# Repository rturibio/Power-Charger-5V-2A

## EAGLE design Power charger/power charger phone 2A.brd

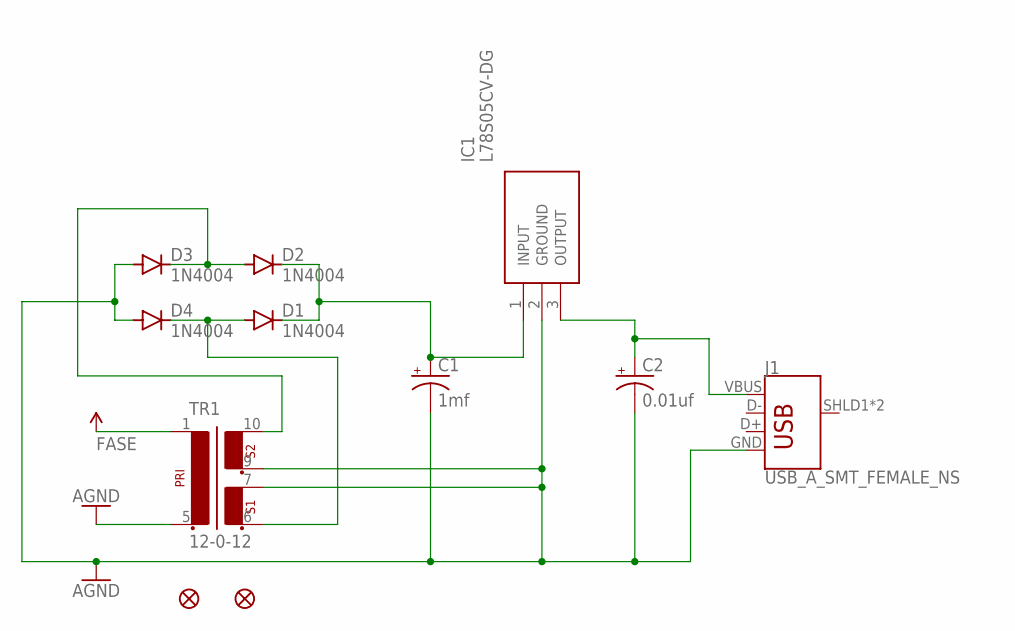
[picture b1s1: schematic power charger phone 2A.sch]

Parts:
C1: 1mf; CPOL-RADIAL-5MM-10MM-KIT
C2: 0.01uf; CPOL-RADIAL-5MM-10MM-KIT
D1, D2, D3, D4: 1N4004; DO41-10
FD1, FD2: FIDUCIAL1X2; FIDUCIAL-1X2
IC1: L78S05CV-DG; TO270P460X1020X2008-3P
J1: USB_A_SMT_FEMALE_NS; USB-A-S-NOSILK-FEMALE
TR1: 12-0-12; EI30-2

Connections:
AGND: C1.-, C2.-, D3.A, D4.A, IC1.2 (GROUND), J1.GND, TR1.5 (2), TR1.7 (4), TR1.9 (5)
FASE: TR1.1
unnamed: C2.+, IC1.3 (OUTPUT), J1.VBUS
unnamed: D2.A, D3.C, TR1.10 (6)
unnamed: D1.A, D4.C, TR1.6 (3)
unnamed: C1.+, D1.C, D2.C, IC1.1 (INPUT)

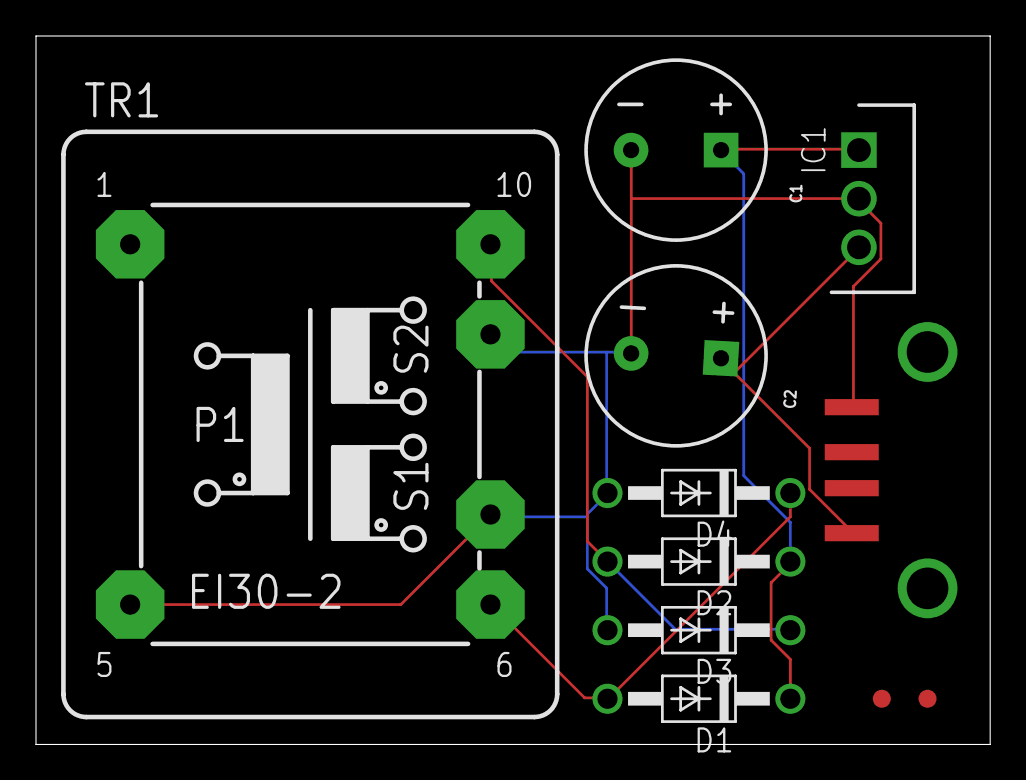
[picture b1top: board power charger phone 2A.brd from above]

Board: 2 copper layers, 53.0 x 39.4 mm, 11 parts (0 on the bottom side), 5 nets.

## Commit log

2022-12-01 Envio de versão final do carregador
    Versão final carregador de 5V 2A

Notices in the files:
parts and their libraries:
SparkFun-Capacitors: Licensing: Creative Commons ShareAlike 4.0 International - https://creativecommons.org/licenses/by-sa/4.0
